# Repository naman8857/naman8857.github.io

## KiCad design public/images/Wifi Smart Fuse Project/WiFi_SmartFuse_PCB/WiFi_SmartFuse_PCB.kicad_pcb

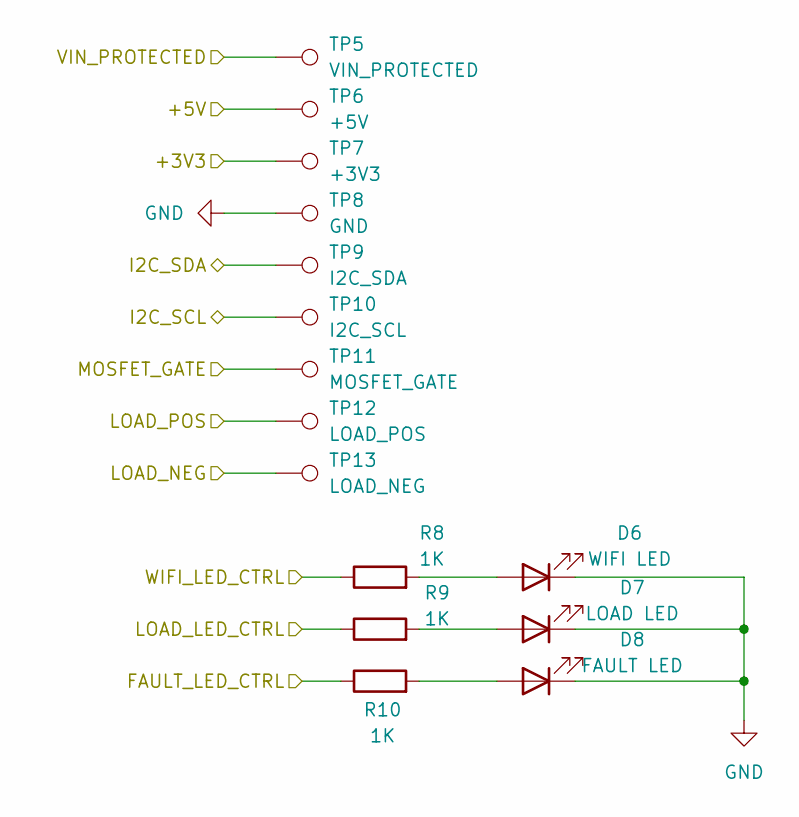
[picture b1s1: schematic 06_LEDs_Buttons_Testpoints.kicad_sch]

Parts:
D6: WIFI LED; LED_0805_2012Metric
D7: LOAD LED; LED_0805_2012Metric
D8: FAULT LED; LED_0805_2012Metric
R8, R9, R10: 1K; R_0805_2012Metric
TP5: VIN_PROTECTED; TestPoint_Pad_D1.5mm
TP6: +5V; TestPoint_Pad_D1.5mm
TP7: +3V3; TestPoint_Pad_D1.5mm
TP8: GND; TestPoint_Pad_D1.5mm
TP9: I2C_SDA; TestPoint_Pad_D1.5mm
TP10: I2C_SCL; TestPoint_Pad_D1.5mm
TP11: MOSFET_GATE; TestPoint_Pad_D1.5mm
TP12: LOAD_POS; TestPoint_Pad_D1.5mm
TP13: LOAD_NEG; TestPoint_Pad_D1.5mm

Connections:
/+3V3: TP7.1; also elsewhere on the board
/+5V: TP6.1; also elsewhere on the board
/FAULT_LED_CTRL: R10.1; also elsewhere on the board
/I2C_SCL: TP10.1; also elsewhere on the board
/I2C_SDA: TP9.1; also elsewhere on the board
/LOAD_LED_CTRL: R9.1; also elsewhere on the board
/LOAD_NEG: TP13.1; also elsewhere on the board
/LOAD_POS: TP12.1; also elsewhere on the board
/MOSFET_GATE: TP11.1; also elsewhere on the board
/VIN_PROTECTED: TP5.1; also elsewhere on the board
/WIFI_LED_CTRL: R8.1; also elsewhere on the board
GND: D6.1 (K), D7.1 (K), D8.1 (K), TP8.1; also elsewhere on the board
unnamed: D6.2 (A), R8.2
unnamed: D7.2 (A), R9.2
unnamed: D8.2 (A), R10.2

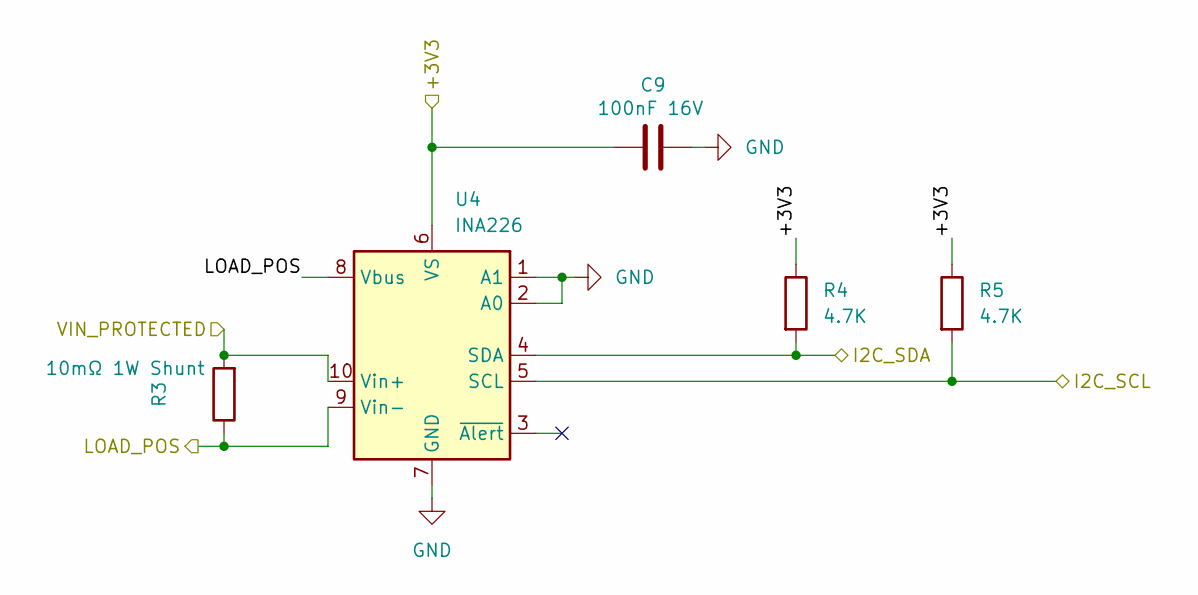
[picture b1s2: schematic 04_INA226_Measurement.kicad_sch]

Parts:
C9: 100nF 16V; C_0805_2012Metric
R3: 10mΩ 1W Shunt; R_2512_6332Metric
R4, R5: 4.7K; R_0805_2012Metric
U4: INA226; VSSOP-10_3x3mm_P0.5mm

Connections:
/+3V3: C9.1, R4.1, R5.1, U4.6 (VS); also elsewhere on the board
/I2C_SCL: R5.2, U4.5 (SCL); also elsewhere on the board
/I2C_SDA: R4.2, U4.4 (SDA); also elsewhere on the board
/LOAD_POS: R3.1, U4.8 (Vbus), U4.9 (Vin-); also elsewhere on the board
/VIN_PROTECTED: R3.2, U4.10 (Vin+); also elsewhere on the board
GND: C9.2, U4.1 (A1), U4.2 (A0), U4.7 (GND); also elsewhere on the board

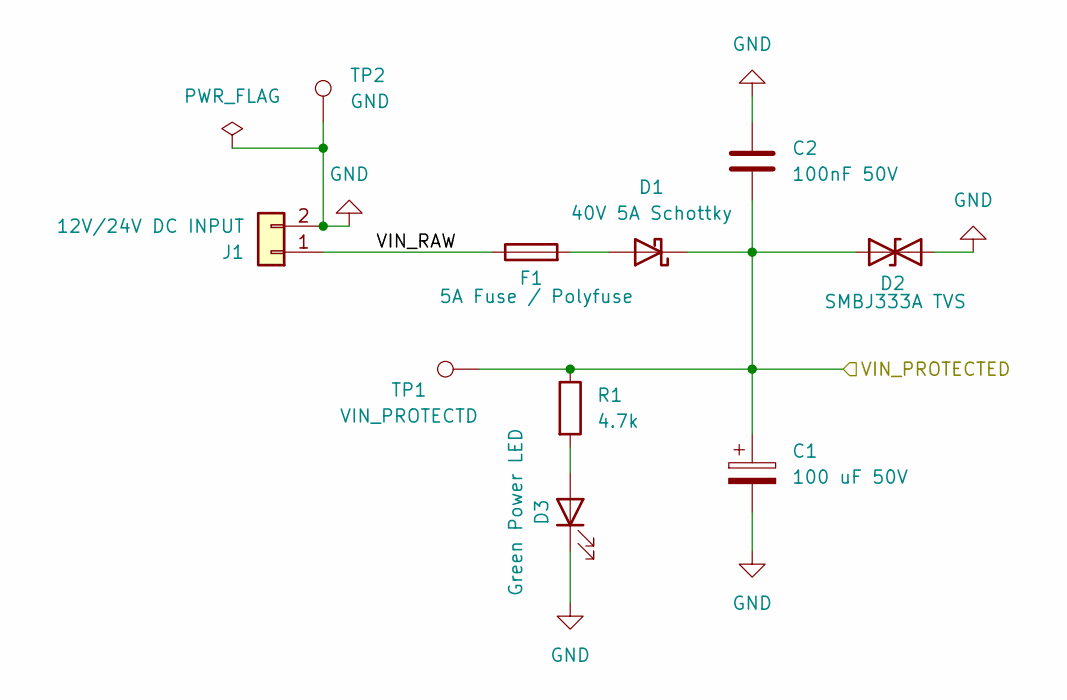
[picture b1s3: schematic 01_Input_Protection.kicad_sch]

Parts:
C1: 100 uF 50V; CP_Radial_D8.0mm_P3.50mm
C2: 100nF 50V; C_0805_2012Metric
D1: 40V 5A Schottky; D_SMC
D2: SMBJ333A TVS; D_SMB
D3: Green Power LED; LED_0805_2012Metric
F1: 5A Fuse / Polyfuse; Fuse_2920_7451Metric
J1: 12V/24V DC INPUT; TerminalBlock_MaiXu_MX126-5.0-02P_1x02_P5.00mm
R1: 4.7k; R_0805_2012Metric
TP1: VIN_PROTECTD; TestPoint_Pad_D1.5mm
TP2: GND; TestPoint_Pad_D1.5mm

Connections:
/01_Input_Protection/VIN_RAW: F1.1, J1.1
/VIN_PROTECTED: C1.1, C2.2, D1.1 (K), D2.1 (A1), R1.1, TP1.1; also elsewhere on the board
GND: C1.2, C2.1, D2.2 (A2), D3.1 (K), J1.2, TP2.1; also elsewhere on the board
unnamed: D1.2 (A), F1.2
unnamed: D3.2 (A), R1.2

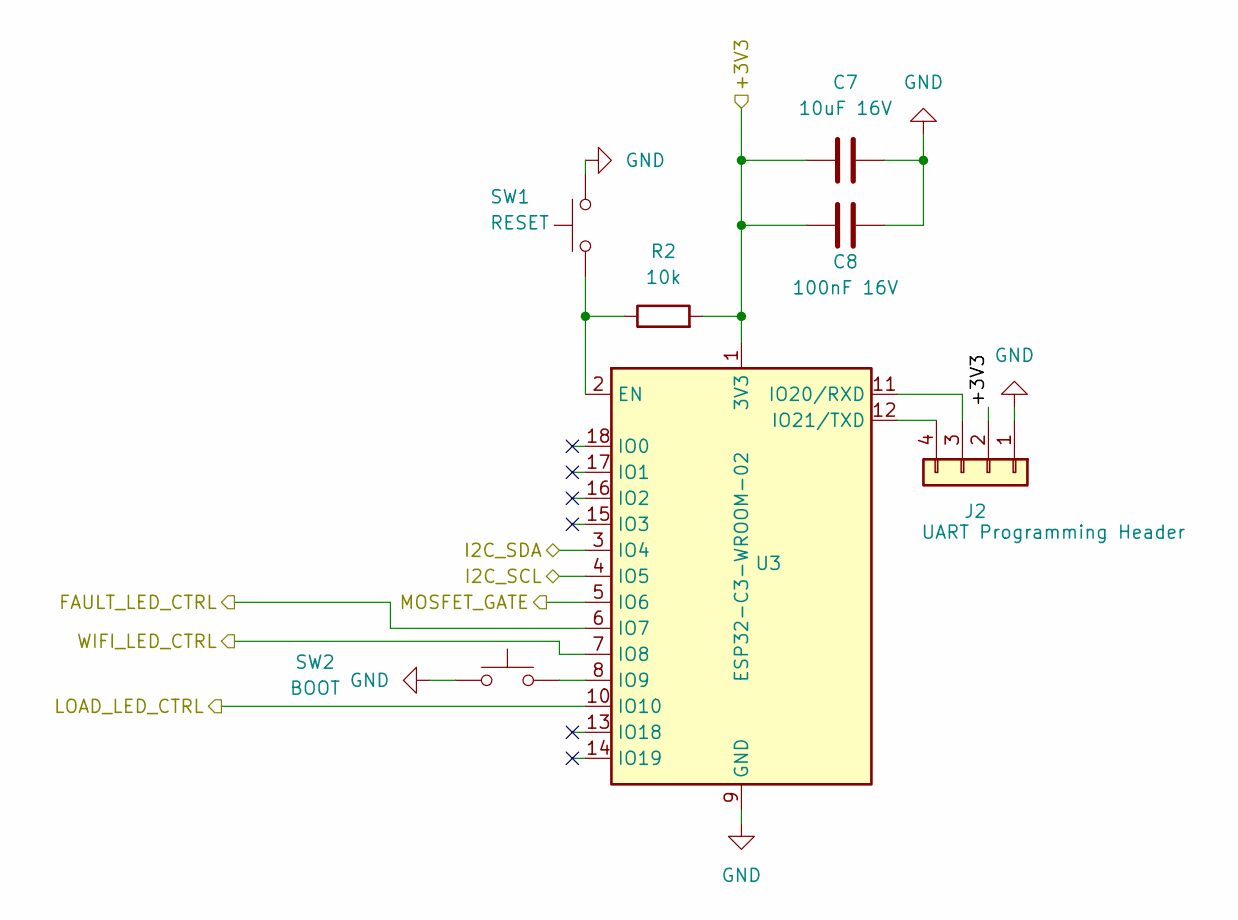
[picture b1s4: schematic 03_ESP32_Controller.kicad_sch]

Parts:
C7: 10uF 16V; C_1206_3216Metric
C8: 100nF 16V; C_0805_2012Metric
J2: UART Programming Header; PinHeader_1x04_P2.54mm_Vertical
R2: 10k; R_0805_2012Metric
SW1: RESET; SW_PUSH_6mm
SW2: BOOT; SW_PUSH_6mm
U3: ESP32-C3-WROOM-02

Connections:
/+3V3: C7.1, C8.1, J2.2, R2.2, U3.1 (3V3); also elsewhere on the board
/FAULT_LED_CTRL: U3.6 (IO7); also elsewhere on the board
/I2C_SCL: U3.4 (IO5); also elsewhere on the board
/I2C_SDA: U3.3 (IO4); also elsewhere on the board
/LOAD_LED_CTRL: U3.10 (IO10); also elsewhere on the board
/MOSFET_GATE: U3.5 (IO6); also elsewhere on the board
/WIFI_LED_CTRL: U3.7 (IO8); also elsewhere on the board
GND: C7.2, C8.2, J2.1, SW1.2, SW2.1, U3.9 (GND), U3.19 (GND); also elsewhere on the board
unnamed: J2.3, U3.11 (IO20/RXD)
unnamed: J2.4, U3.12 (IO21/TXD)
unnamed: R2.1, SW1.1, U3.2 (EN)
unnamed: SW2.2, U3.8 (IO9)

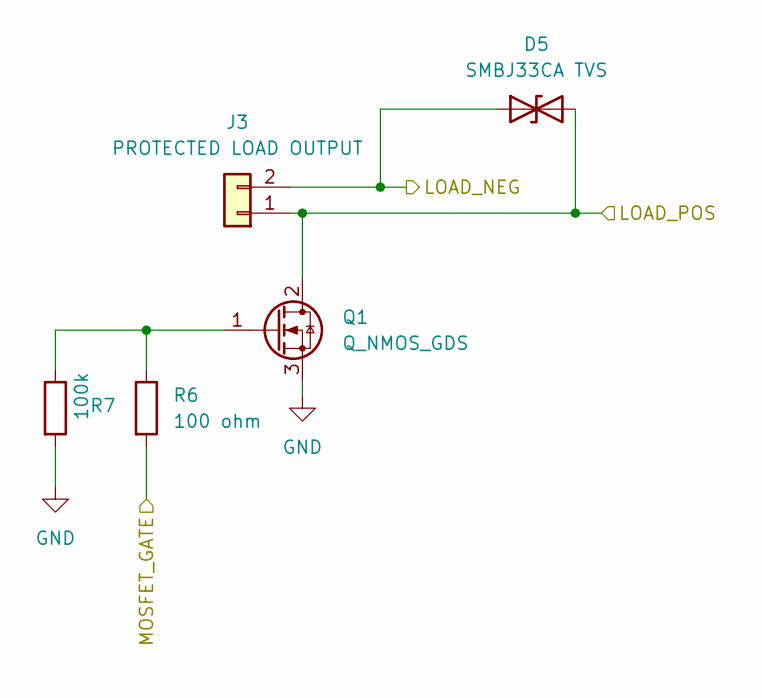
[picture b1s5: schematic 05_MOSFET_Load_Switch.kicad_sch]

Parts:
D5: SMBJ33CA TVS; D_SMB
J3: PROTECTED LOAD OUTPUT; TerminalBlock_MaiXu_MX126-5.0-02P_1x02_P5.00mm
Q1: Q_NMOS_GDS; TO-252-3_TabPin2
R6: 100 ohm; R_0805_2012Metric
R7: 100k; R_0805_2012Metric

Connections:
/LOAD_NEG: D5.1 (A1), J3.2; also elsewhere on the board
/LOAD_POS: D5.2 (A2), J3.1, Q1.2 (D); also elsewhere on the board
/MOSFET_GATE: R6.2; also elsewhere on the board
GND: Q1.3 (S), R7.2; also elsewhere on the board
unnamed: Q1.1 (G), R6.1, R7.1

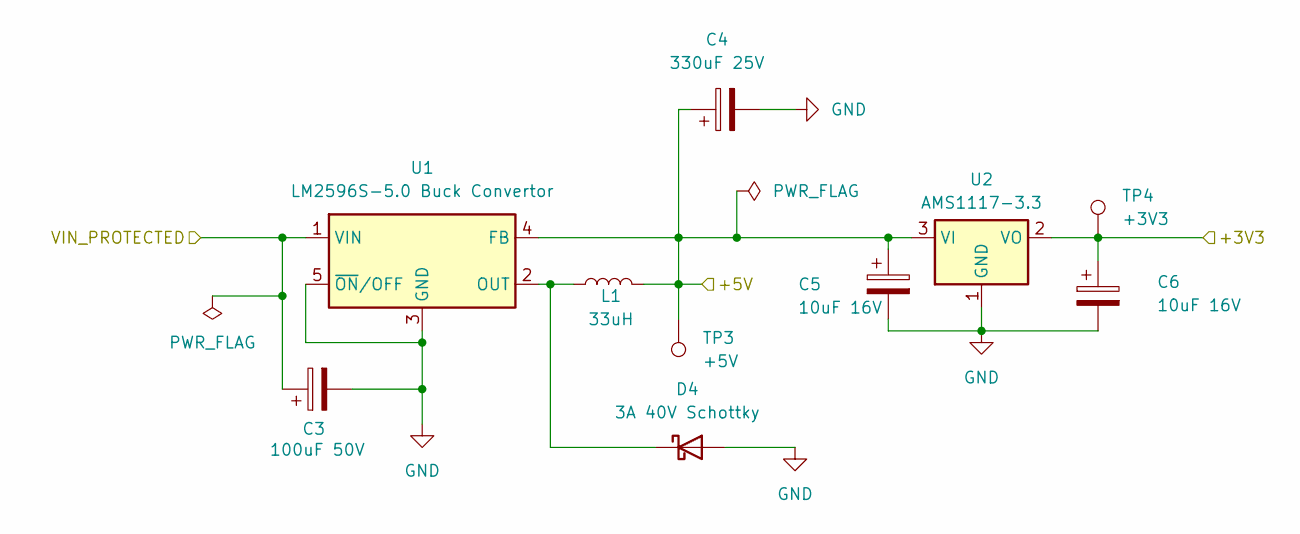
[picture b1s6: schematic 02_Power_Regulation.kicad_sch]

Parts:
C3: 100uF 50V; CP_Radial_D8.0mm_P3.50mm
C4: 330uF 25V; CP_Radial_D10.0mm_P5.00mm
C5, C6: 10uF 16V; C_1206_3216Metric
D4: 3A 40V Schottky; D_SMA
L1: 33uH; L_Bourns_SRP1038C_10.0x10.0mm
TP3: +5V; TestPoint_Pad_D1.5mm
TP4: +3V3; TestPoint_Pad_D1.5mm
U1: LM2596S-5.0 Buck Convertor; TO-263-5_TabPin3
U2: AMS1117-3.3; SOT-223-3_TabPin2

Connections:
/+3V3: C6.1, TP4.1, U2.2 (VO); also elsewhere on the board
/+5V: C4.1, C5.1, L1.2, TP3.1, U1.4 (FB), U2.3 (VI); also elsewhere on the board
/VIN_PROTECTED: C3.1, U1.1 (VIN); also elsewhere on the board
GND: C3.2, C4.2, C5.2, C6.2, D4.2 (A), U1.3 (GND), U1.5 (~ON/OFF), U2.1 (GND); also elsewhere on the board
unnamed: D4.1 (K), L1.1, U1.2 (OUT)

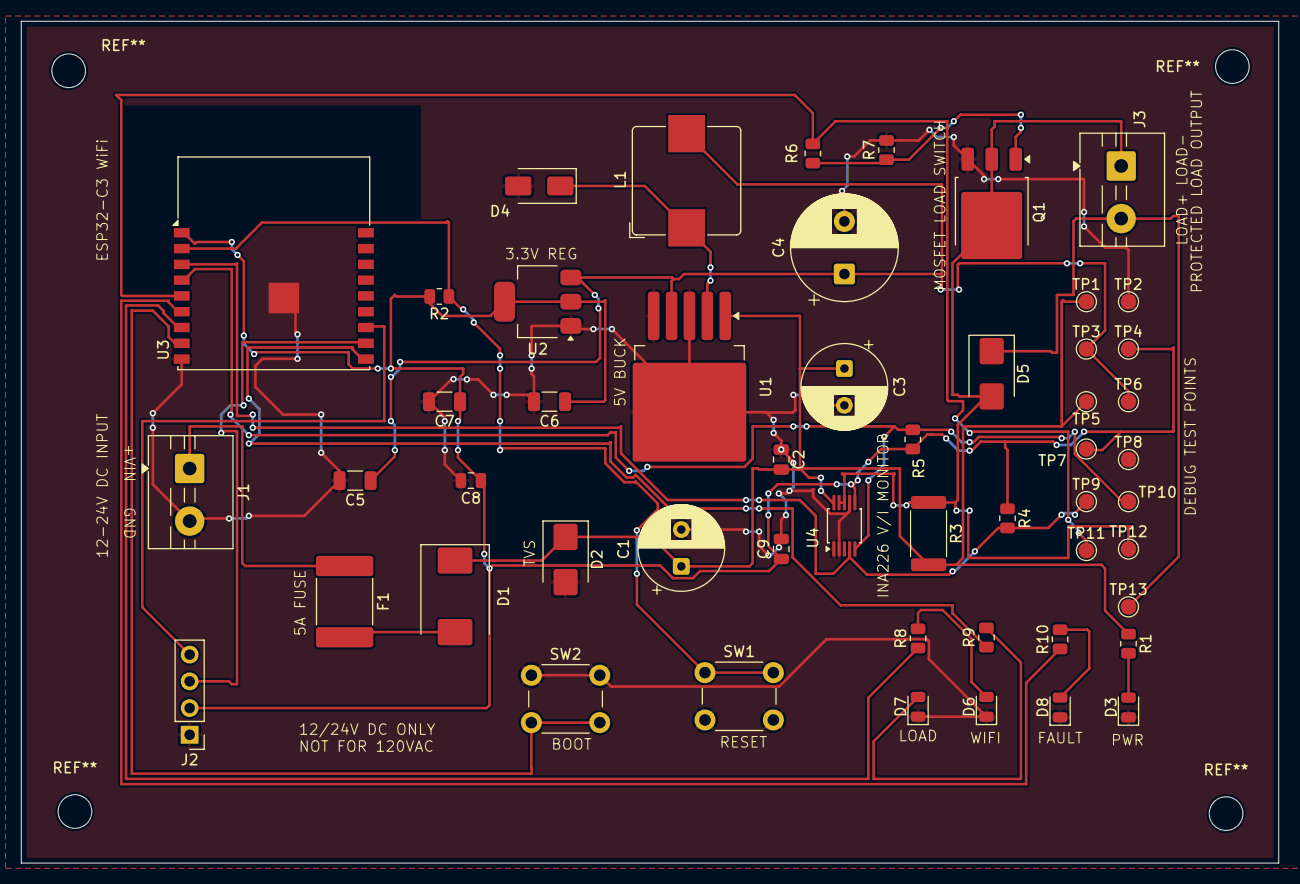
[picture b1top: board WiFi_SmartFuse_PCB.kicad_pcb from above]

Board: 2 copper layers, 119.5 x 80.0 mm, 52 parts (0 on the bottom side), 24 nets.

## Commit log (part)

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2026-05-08 Initial commit from Create Next App
2026-05-20 Prepare repository for GitHub
2026-06-09 Update portfolio page, layout, and globals for deployment
2026-06-11 Polish portfolio hero evidence card
2026-06-17 Refocus portfolio for electrical engineering roles
2026-06-17 Add professional headshot to portfolio hero section with responsive layout
2026-06-17 Update portfolio color scheme to warm amber tones matching professional headshot
2026-06-17 Fix layout and responsiveness: clean design with optimized mobile view and professional headshot
2026-06-17 Replace web resume with actual PDF viewer - shows professional resume document
2026-06-17 Remove test screenshot files to clean up repository
2026-06-17 Optimize image to 29KB for instant mobile loading, fix PDF zoom, update GPA to 3.96, add responsive image sizing
2026-06-17 Remove duplicate name from navigation, keep only NA initials in header
2026-06-17 Move name and title to top navigation only - clean hero section
2026-06-17 Remove proof points section from portfolio
2026-06-17 Remove redundant skill items to eliminate repetition
2026-06-17 Update top navigation to show 'Electrical Engineering Student'
2026-06-17 Make resume page static - fixed aspect ratio with no layout shift on mobile
2026-06-29 Add WiFi SmartFuse project assets
2026-06-29 Add Onshape office workspace project assets
2026-06-29 Update portfolio headshot and project showcase
2026-06-30 Fix portfolio project tiles and project detail pages
2026-06-30 Improve project page engineering summaries
2026-06-30 Improve WiFi SmartFuse project proof page
2026-06-30 Swap WiFi SmartFuse proof images
2026-06-30 Improve child monitoring project page and project order
2026-06-30 Polish child monitoring project page and tile layout
2026-06-30 Improve desktop homepage layout
2026-06-30 Fix desktop homepage layout without changing mobile
